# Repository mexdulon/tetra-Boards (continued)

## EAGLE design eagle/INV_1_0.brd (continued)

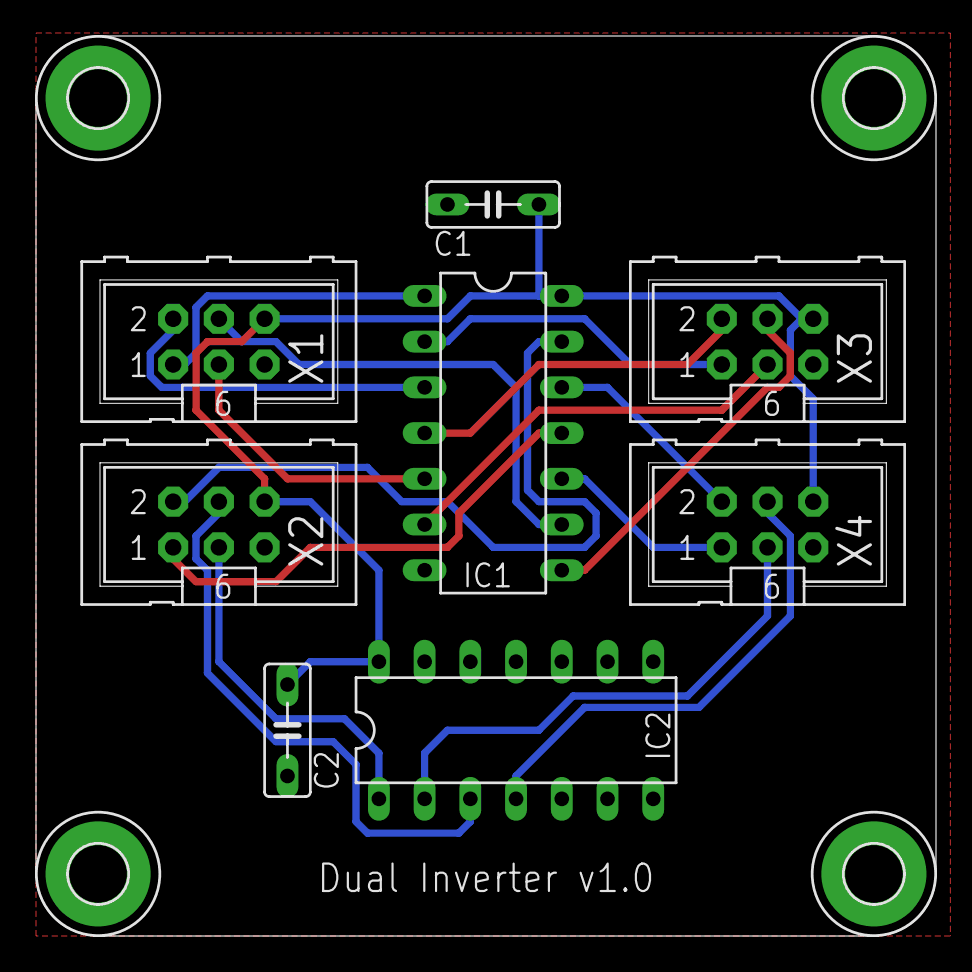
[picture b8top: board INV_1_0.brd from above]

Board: 2 copper layers, 50.0 x 50.0 mm, 12 parts (0 on the bottom side), 18 nets.
